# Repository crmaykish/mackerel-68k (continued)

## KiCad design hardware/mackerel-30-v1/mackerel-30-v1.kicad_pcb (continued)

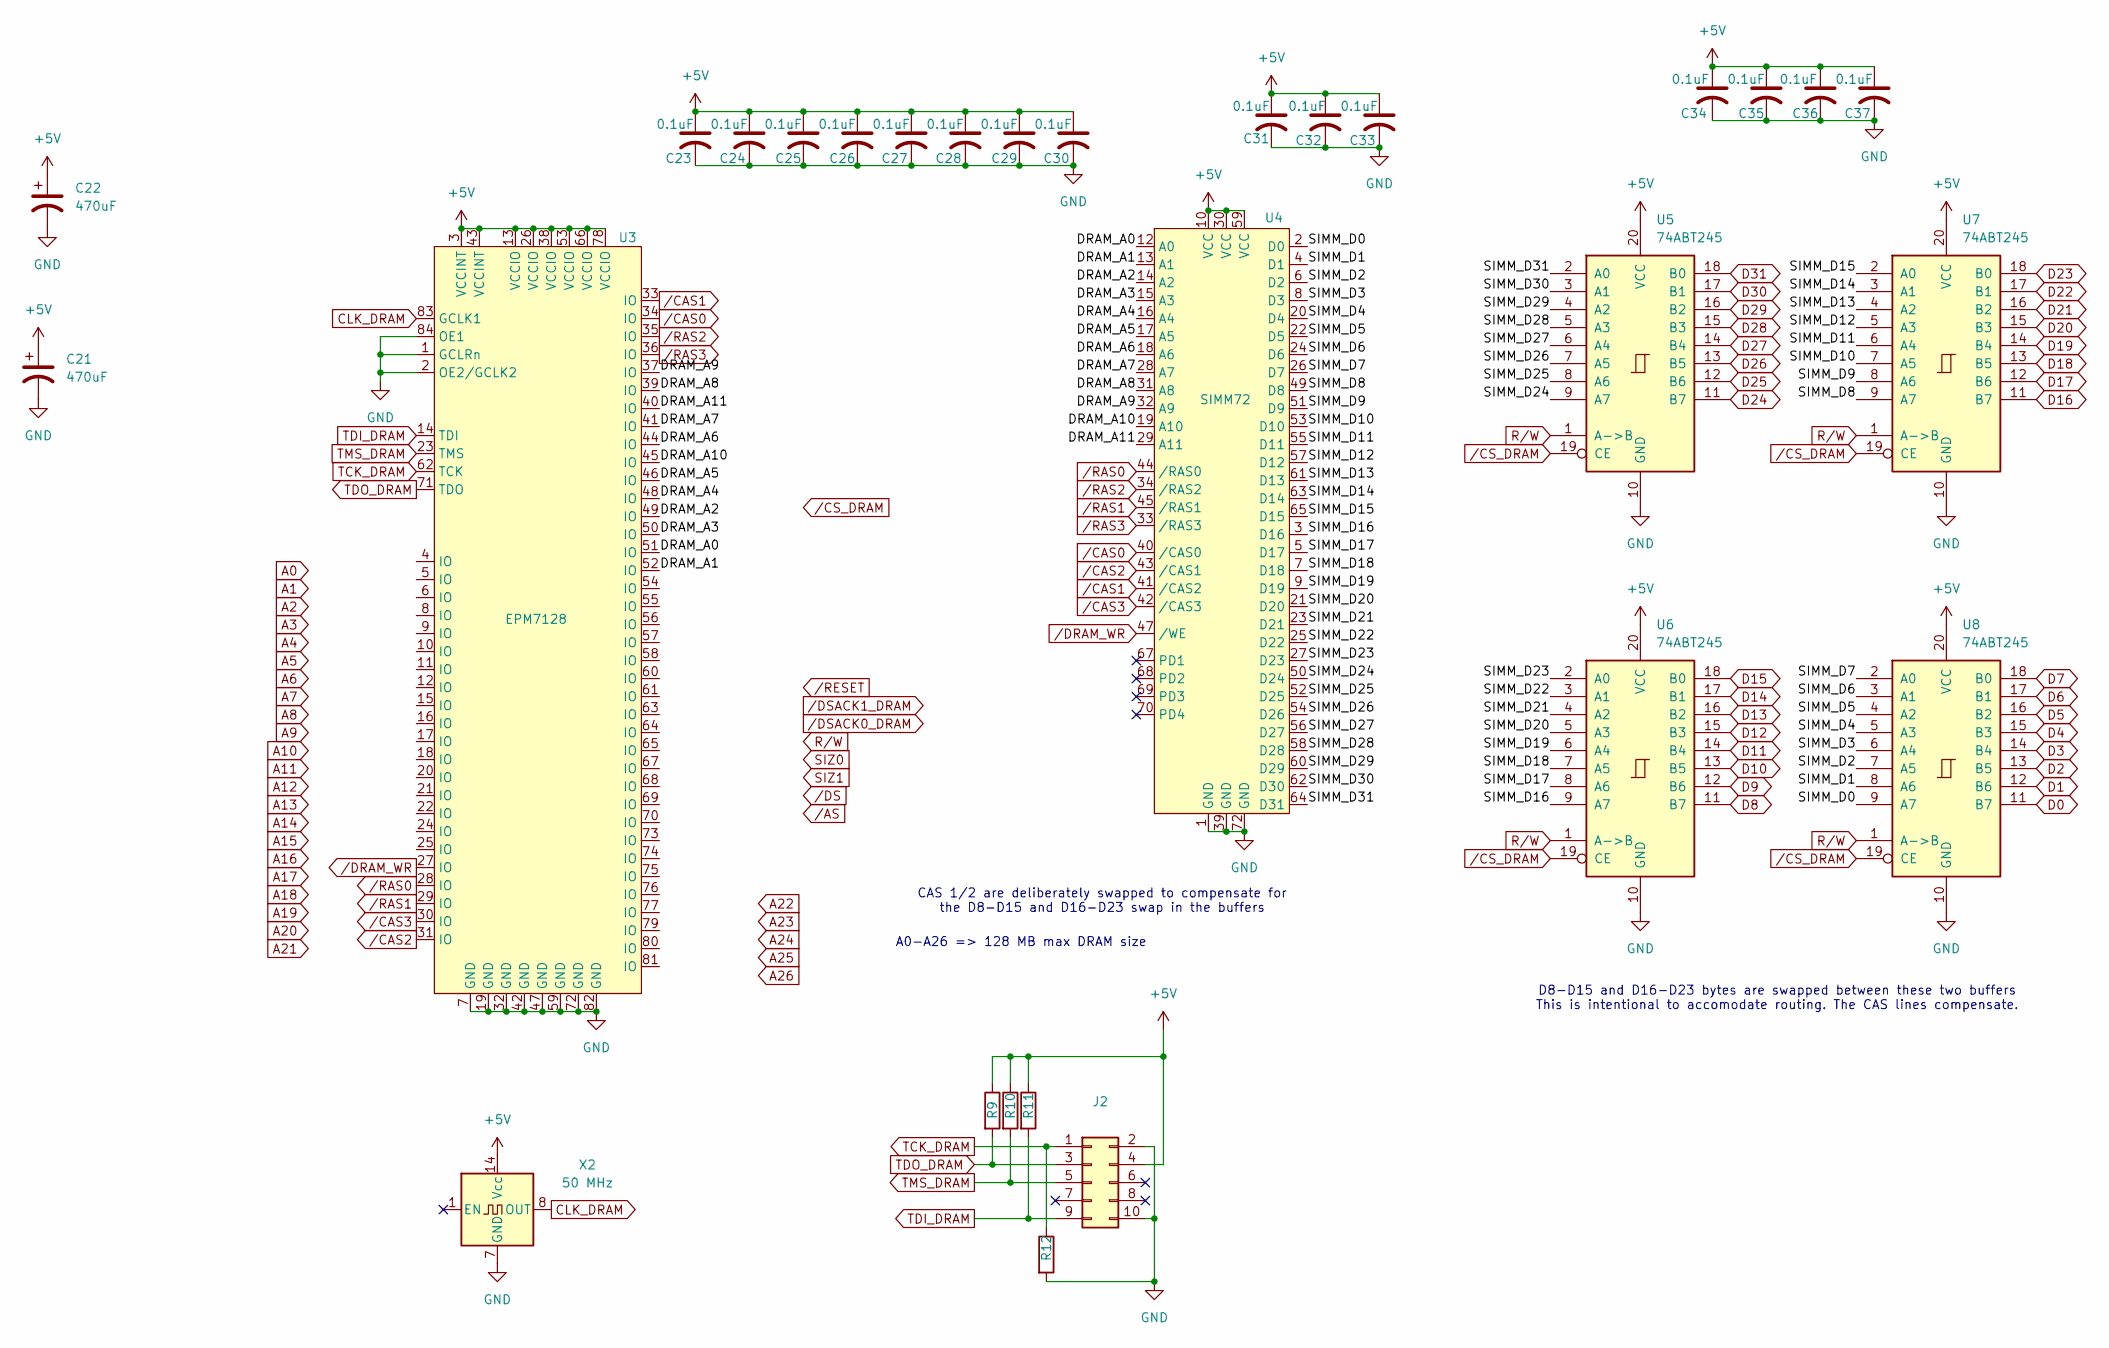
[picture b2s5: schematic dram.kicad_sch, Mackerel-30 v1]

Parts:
C21, C22: 470uF; CP_Radial_D8.0mm_P3.50mm
C23, C24, C25, C26, C27, C28, C29, C30, C31, C32, C33, C34, C35, C36, C37: 0.1uF; C_1206_3216Metric_Pad1.33x1.80mm_HandSolder
J2: Conn_02x05_Odd_Even; IDC-Header_2x05_P2.54mm_Vertical
R9, R10, R11, R12: 4k7; R_1206_3216Metric_Pad1.30x1.75mm_HandSolder
U3: EPM7128; PLCC-84_THT-Socket
U4: SIMM72; SIMM-72
U5, U6, U7, U8: 74ABT245; DIP-20_W7.62mm_Socket_LongPads
X2: 50 MHz; Oscillator_DIP-14

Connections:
+5V: C21.1, C22.1, C23.1, C24.1, C25.1, C26.1, C27.1, C28.1, C29.1, C30.1, C31.1, C32.1, C33.1, C34.1, C35.1, C36.1, C37.1, J2.4, R9.1, R10.1, R11.1, U3.3 (VCCINT), U3.13 (VCCIO), U3.26 (VCCIO), U3.38 (VCCIO), U3.43 (VCCINT), U3.53 (VCCIO), U3.66 (VCCIO), U3.78 (VCCIO), U4.10 (VCC), U4.30 (VCC), U4.59 (VCC), U5.20 (VCC), U6.20 (VCC), U7.20 (VCC), U8.20 (VCC), X2.14 (Vcc); also elsewhere on the board
/DRAM/DRAM_A0: U3.51 (IO), U4.12 (A0)
/DRAM/DRAM_A1: U3.52 (IO), U4.13 (A1)
/DRAM/DRAM_A2: U3.49 (IO), U4.14 (A2)
/DRAM/DRAM_A3: U3.50 (IO), U4.15 (A3)
/DRAM/DRAM_A4: U3.48 (IO), U4.16 (A4)
/DRAM/DRAM_A5: U3.46 (IO), U4.17 (A5)
/DRAM/DRAM_A6: U3.44 (IO), U4.18 (A6)
/DRAM/DRAM_A7: U3.41 (IO), U4.28 (A7)
/DRAM/DRAM_A8: U3.39 (IO), U4.31 (A8)
/DRAM/DRAM_A9: U3.37 (IO), U4.32 (A9)
/DRAM/DRAM_A10: U3.45 (IO), U4.19 (A10)
/DRAM/DRAM_A11: U3.40 (IO), U4.29 (A11)
/DRAM/SIMM_D0: U4.2 (D0), U8.9 (A7)
/DRAM/SIMM_D1: U4.4 (D1), U8.8 (A6)
/DRAM/SIMM_D2: U4.6 (D2), U8.7 (A5)
/DRAM/SIMM_D3: U4.8 (D3), U8.6 (A4)
/DRAM/SIMM_D4: U4.20 (D4), U8.5 (A3)
/DRAM/SIMM_D5: U4.22 (D5), U8.4 (A2)
/DRAM/SIMM_D6: U4.24 (D6), U8.3 (A1)
/DRAM/SIMM_D7: U4.26 (D7), U8.2 (A0)
/DRAM/SIMM_D8: U4.49 (D8), U7.9 (A7)
/DRAM/SIMM_D9: U4.51 (D9), U7.8 (A6)
/DRAM/SIMM_D10: U4.53 (D10), U7.7 (A5)
/DRAM/SIMM_D11: U4.55 (D11), U7.6 (A4)
/DRAM/SIMM_D12: U4.57 (D12), U7.5 (A3)
/DRAM/SIMM_D13: U4.61 (D13), U7.4 (A2)
/DRAM/SIMM_D14: U4.63 (D14), U7.3 (A1)
/DRAM/SIMM_D15: U4.65 (D15), U7.2 (A0)
/DRAM/SIMM_D16: U4.3 (D16), U6.9 (A7)
/DRAM/SIMM_D17: U4.5 (D17), U6.8 (A6)
/DRAM/SIMM_D18: U4.7 (D18), U6.7 (A5)
/DRAM/SIMM_D19: U4.9 (D19), U6.6 (A4)
/DRAM/SIMM_D20: U4.21 (D20), U6.5 (A3)
/DRAM/SIMM_D21: U4.23 (D21), U6.4 (A2)
/DRAM/SIMM_D22: U4.25 (D22), U6.3 (A1)
/DRAM/SIMM_D23: U4.27 (D23), U6.2 (A0)
/DRAM/SIMM_D24: U4.50 (D24), U5.9 (A7)
/DRAM/SIMM_D25: U4.52 (D25), U5.8 (A6)
/DRAM/SIMM_D26: U4.54 (D26), U5.7 (A5)
/DRAM/SIMM_D27: U4.56 (D27), U5.6 (A4)
/DRAM/SIMM_D28: U4.58 (D28), U5.5 (A3)
/DRAM/SIMM_D29: U4.60 (D29), U5.4 (A2)
/DRAM/SIMM_D30: U4.62 (D30), U5.3 (A1)
/DRAM/SIMM_D31: U4.64 (D31), U5.2 (A0)
CLK_DRAM: U3.83 (GCLK1), X2.8 (OUT)
D0: U8.11 (B7); also elsewhere on the board
D1: U8.12 (B6); also elsewhere on the board
D2: U8.13 (B5); also elsewhere on the board
D3: U8.14 (B4); also elsewhere on the board
D4: U8.15 (B3); also elsewhere on the board
D5: U8.16 (B2); also elsewhere on the board
D6: U8.17 (B1); also elsewhere on the board
D7: U8.18 (B0); also elsewhere on the board
D8: U6.11 (B7); also elsewhere on the board
D9: U6.12 (B6); also elsewhere on the board
D10: U6.13 (B5); also elsewhere on the board
D11: U6.14 (B4); also elsewhere on the board
D12: U6.15 (B3); also elsewhere on the board
D13: U6.16 (B2); also elsewhere on the board
D14: U6.17 (B1); also elsewhere on the board
D15: U6.18 (B0); also elsewhere on the board
D16: U7.11 (B7); also elsewhere on the board
D17: U7.12 (B6); also elsewhere on the board
D18: U7.13 (B5); also elsewhere on the board
D19: U7.14 (B4); also elsewhere on the board
D20: U7.15 (B3); also elsewhere on the board
D21: U7.16 (B2); also elsewhere on the board
D22: U7.17 (B1); also elsewhere on the board
D23: U7.18 (B0); also elsewhere on the board
D24: U5.11 (B7); also elsewhere on the board
D25: U5.12 (B6); also elsewhere on the board
D26: U5.13 (B5); also elsewhere on the board
D27: U5.14 (B4); also elsewhere on the board
D28: U5.15 (B3); also elsewhere on the board
D29: U5.16 (B2); also elsewhere on the board
D30: U5.17 (B1); also elsewhere on the board
D31: U5.18 (B0); also elsewhere on the board
GND: C21.2, C22.2, C23.2, C24.2, C25.2, C26.2, C27.2, C28.2, C29.2, C30.2, C31.2, C32.2, C33.2, C34.2, C35.2, C36.2, C37.2, J2.2, J2.10, R12.2, U3.1 (GCLRn), U3.2 (OE2/GCLK2), U3.7 (GND), U3.19 (GND), U3.32 (GND), U3.42 (GND), U3.47 (GND), U3.59 (GND), U3.72 (GND), U3.82 (GND), U3.84 (OE1), U4.1 (GND), U4.39 (GND), U4.72 (GND), U5.10 (GND), U6.10 (GND), U7.10 (GND), U8.10 (GND), X2.7 (GND); also elsewhere on the board
R/W: U5.1 (A->B), U6.1 (A->B), U7.1 (A->B), U8.1 (A->B); also elsewhere on the board
TCK_DRAM: J2.1, R12.1, U3.62 (TCK)
TDI_DRAM: J2.9, R11.2, U3.14 (TDI)
TDO_DRAM: J2.3, R9.2, U3.71 (TDO)
TMS_DRAM: J2.5, R10.2, U3.23 (TMS)
/CAS0: U3.34 (IO), U4.40 (/CAS0)
/CAS1: U3.33 (IO), U4.41 (/CAS2)
/CAS2: U3.31 (IO), U4.43 (/CAS1)
/CAS3: U3.30 (IO), U4.42 (/CAS3)
/CS_DRAM: U5.19 (CE), U6.19 (CE), U7.19 (CE), U8.19 (CE)
/DRAM_WR: U3.27 (IO), U4.47 (/WE)
/RAS0: U3.28 (IO), U4.44 (/RAS0)
/RAS1: U3.29 (IO), U4.45 (/RAS1)
/RAS2: U3.35 (IO), U4.34 (/RAS2)
/RAS3: U3.36 (IO), U4.33 (/RAS3)

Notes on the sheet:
A0-A26 => 128 MB max DRAM size
CAS 1/2 are deliberately swapped to compensate for the D8-D15 and D16-D23 swap in the buffers
D8-D15 and D16-D23 bytes are swapped between these two buffers This is intentional to accomodate routing. The CAS lines compensate.

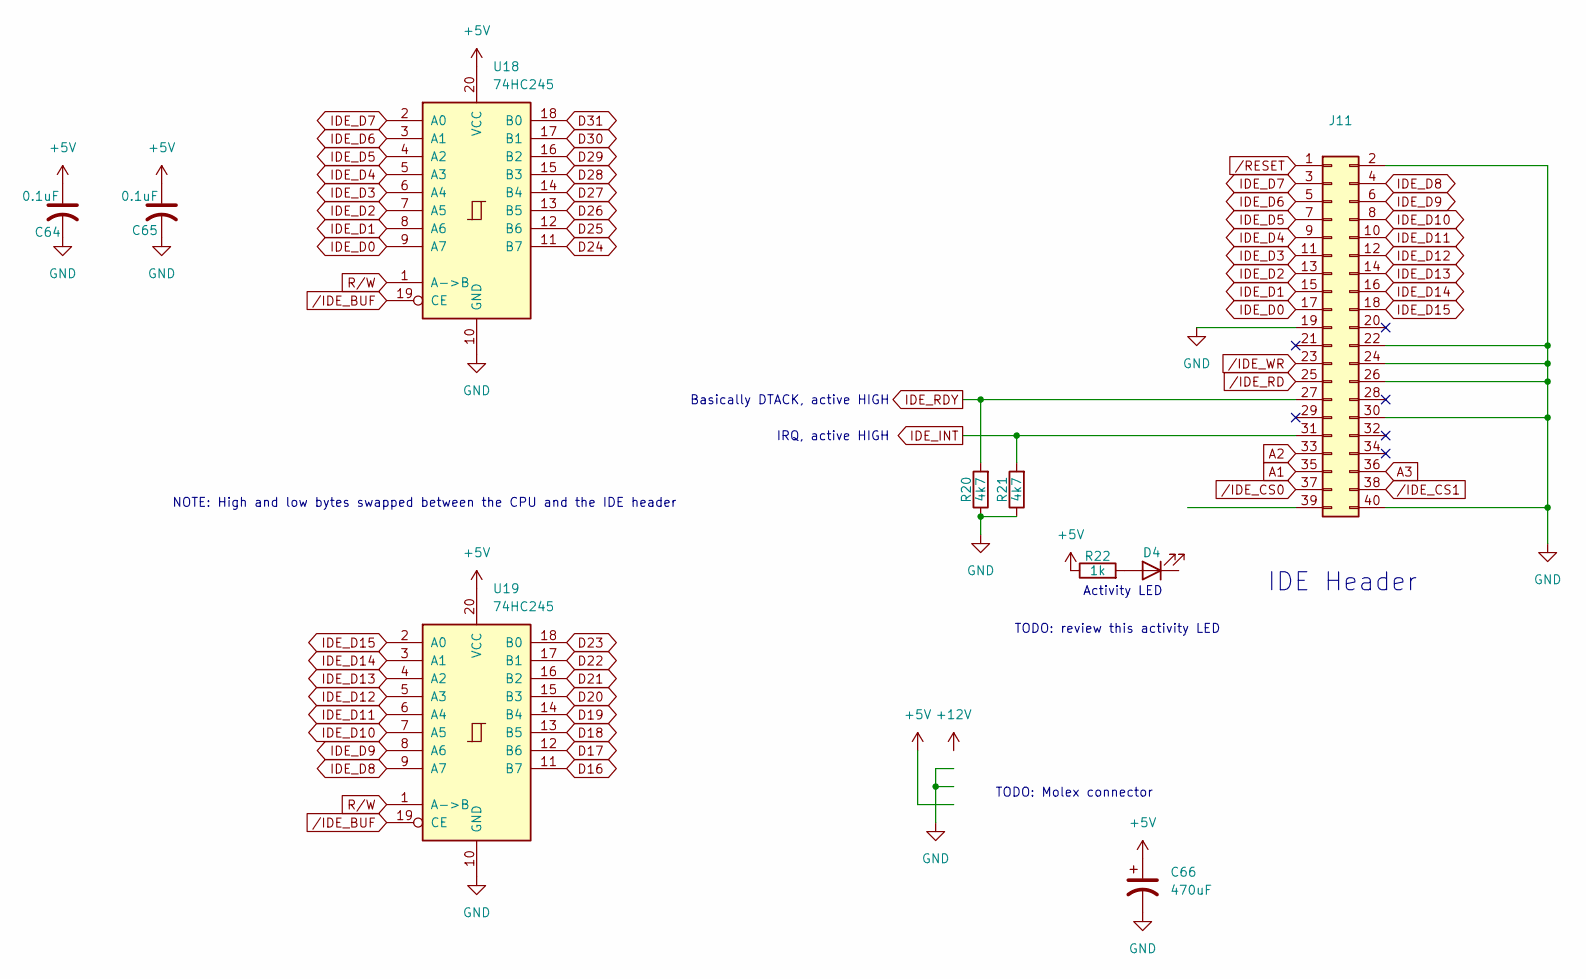
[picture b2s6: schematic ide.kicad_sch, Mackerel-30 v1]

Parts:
C64, C65: 0.1uF; C_1206_3216Metric_Pad1.33x1.80mm_HandSolder
C66: 470uF; CP_Radial_D8.0mm_P3.50mm
D4: LED; LED_D5.0mm
J11: Conn_02x20_Odd_Even; IDC-Header_2x20_P2.54mm_Vertical
R20, R21: 4k7; R_1206_3216Metric_Pad1.30x1.75mm_HandSolder
R22: 1k; R_1206_3216Metric_Pad1.30x1.75mm_HandSolder
U18, U19: 74HC245; DIP-20_W7.62mm_Socket

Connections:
+5V: C64.1, C65.1, C66.1, R22.1, U18.20 (VCC), U19.20 (VCC); also elsewhere on the board
A1: J11.35; also elsewhere on the board
A2: J11.33; also elsewhere on the board
A3: J11.36; also elsewhere on the board
D16: U19.11 (B7); also elsewhere on the board
D17: U19.12 (B6); also elsewhere on the board
D18: U19.13 (B5); also elsewhere on the board
D19: U19.14 (B4); also elsewhere on the board
D20: U19.15 (B3); also elsewhere on the board
D21: U19.16 (B2); also elsewhere on the board
D22: U19.17 (B1); also elsewhere on the board
D23: U19.18 (B0); also elsewhere on the board
D24: U18.11 (B7); also elsewhere on the board
D25: U18.12 (B6); also elsewhere on the board
D26: U18.13 (B5); also elsewhere on the board
D27: U18.14 (B4); also elsewhere on the board
D28: U18.15 (B3); also elsewhere on the board
D29: U18.16 (B2); also elsewhere on the board
D30: U18.17 (B1); also elsewhere on the board
D31: U18.18 (B0); also elsewhere on the board
GND: C64.2, C65.2, C66.2, J11.2, J11.19, J11.22, J11.24, J11.26, J11.30, J11.40, R20.1, R21.1, U18.10 (GND), U19.10 (GND); also elsewhere on the board
IDE_D0: J11.17, U18.9 (A7)
IDE_D1: J11.15, U18.8 (A6)
IDE_D2: J11.13, U18.7 (A5)
IDE_D3: J11.11, U18.6 (A4)
IDE_D4: J11.9, U18.5 (A3)
IDE_D5: J11.7, U18.4 (A2)
IDE_D6: J11.5, U18.3 (A1)
IDE_D7: J11.3, U18.2 (A0)
IDE_D8: J11.4, U19.9 (A7)
IDE_D9: J11.6, U19.8 (A6)
IDE_D10: J11.8, U19.7 (A5)
IDE_D11: J11.10, U19.6 (A4)
IDE_D12: J11.12, U19.5 (A3)
IDE_D13: J11.14, U19.4 (A2)
IDE_D14: J11.16, U19.3 (A1)
IDE_D15: J11.18, U19.2 (A0)
IDE_INT: J11.31, R21.2
IDE_RDY: J11.27, R20.2
unnamed: D4.2 (A_2), R22.2
R/W: U18.1 (A->B), U19.1 (A->B); also elsewhere on the board
/IDE_BUF: U18.19 (CE), U19.19 (CE)
/IDE_CS0: J11.37
/IDE_CS1: J11.38
/IDE_RD: J11.25
/IDE_WR: J11.23
/RESET: J11.1; also elsewhere on the board

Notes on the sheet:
IDE Header
TODO: Molex connector
IRQ, active HIGH
NOTE: High and low bytes swapped between the CPU and the IDE header
TODO: review this activity LED
Basically DTACK, active HIGH
Activity LED

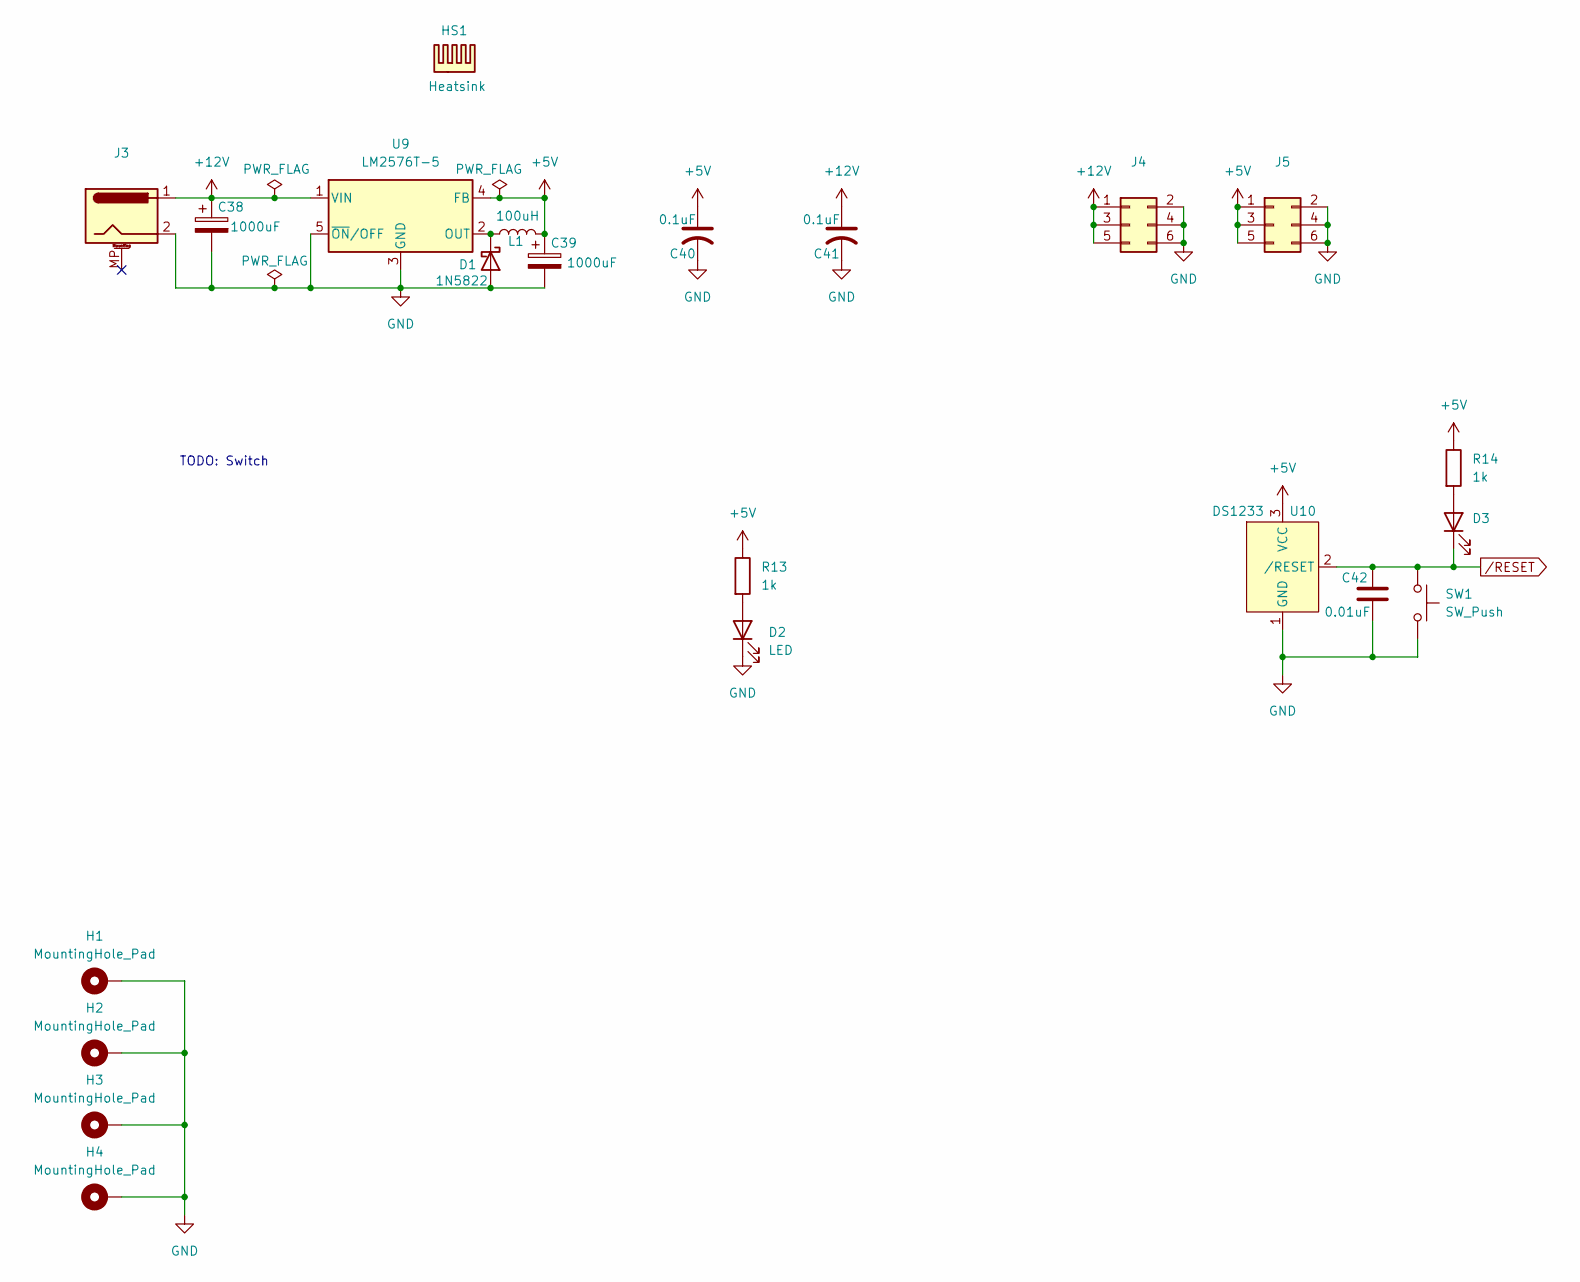
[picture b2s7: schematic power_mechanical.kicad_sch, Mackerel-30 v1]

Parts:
C38, C39: 1000uF; CP_Radial_D10.0mm_P5.00mm
C40, C41: 0.1uF; C_1206_3216Metric_Pad1.33x1.80mm_HandSolder
C42: 0.01uF; C_1206_3216Metric_Pad1.33x1.80mm_HandSolder
D1: 1N5822; D_DO-27_P15.24mm_Horizontal
D2, D3: LED; LED_D5.0mm
H1, H2, H3, H4: MountingHole_Pad; MountingHole_3.2mm_M3_Pad_Via
HS1: Heatsink; Heatsink_Stonecold_HS-S02_13.21x9.53mm
J3: Barrel_Jack_MountingPin; BarrelJack_Horizontal
J4, J5: Conn_02x03_Odd_Even; PinHeader_2x03_P2.54mm_Vertical
L1: 100uH; L_Radial_D10.0mm_P5.00mm_Fastron_07M
R13, R14: 1k; R_1206_3216Metric_Pad1.30x1.75mm_HandSolder
SW1: SW_Push; SW_PUSH_6mm_H5mm
U9: LM2576T-5; TO-220-5_Vertical
U10: DS1233; TO-92L_Wide

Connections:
+5V: C39.1, C40.1, J5.1, J5.3, J5.5, L1.2, R13.1, R14.1, U9.4 (FB), U10.3 (VCC); also elsewhere on the board
+12V: C38.1, C41.1, J3.1, J4.1, J4.3, J4.5, U9.1 (VIN)
GND: C38.2, C39.2, C40.2, C41.2, C42.2, D1.2 (A), D2.1 (K), H1.1 (1_1), H2.1 (1_1), H3.1 (1_1), H4.1 (1_1), J3.2, J4.2, J4.4, J4.6, J5.2, J5.4, J5.6, SW1.2, U9.3 (GND), U9.5 (~ON/OFF), U10.1 (GND); also elsewhere on the board
unnamed: D1.1 (K), L1.1, U9.2 (OUT)
unnamed: D2.2 (A), R13.2
unnamed: D3.2 (A), R14.2
/RESET: C42.1, D3.1 (K), SW1.1, U10.2 (/RESET); also elsewhere on the board

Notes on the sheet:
TODO: Switch

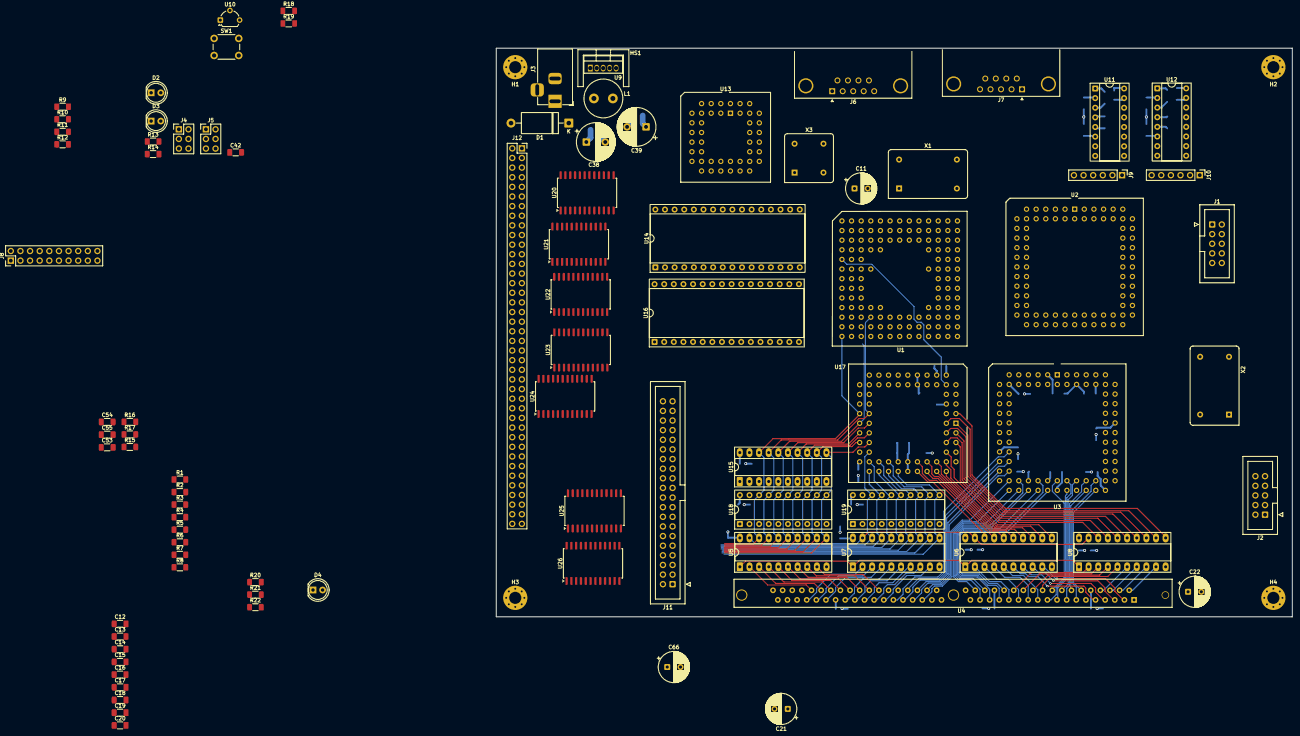
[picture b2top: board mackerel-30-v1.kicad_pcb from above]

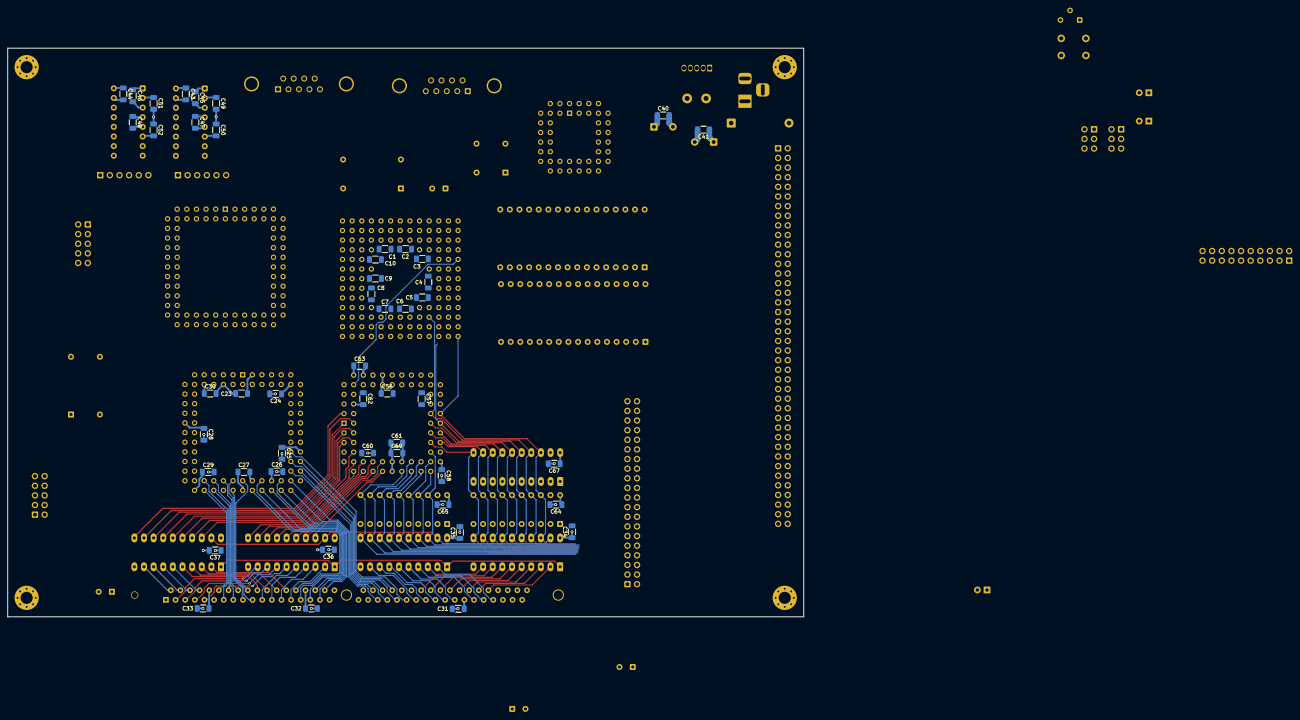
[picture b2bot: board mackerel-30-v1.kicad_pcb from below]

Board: 4 copper layers, 210.0 x 150.0 mm, 141 parts (48 on the bottom side), 215 nets.

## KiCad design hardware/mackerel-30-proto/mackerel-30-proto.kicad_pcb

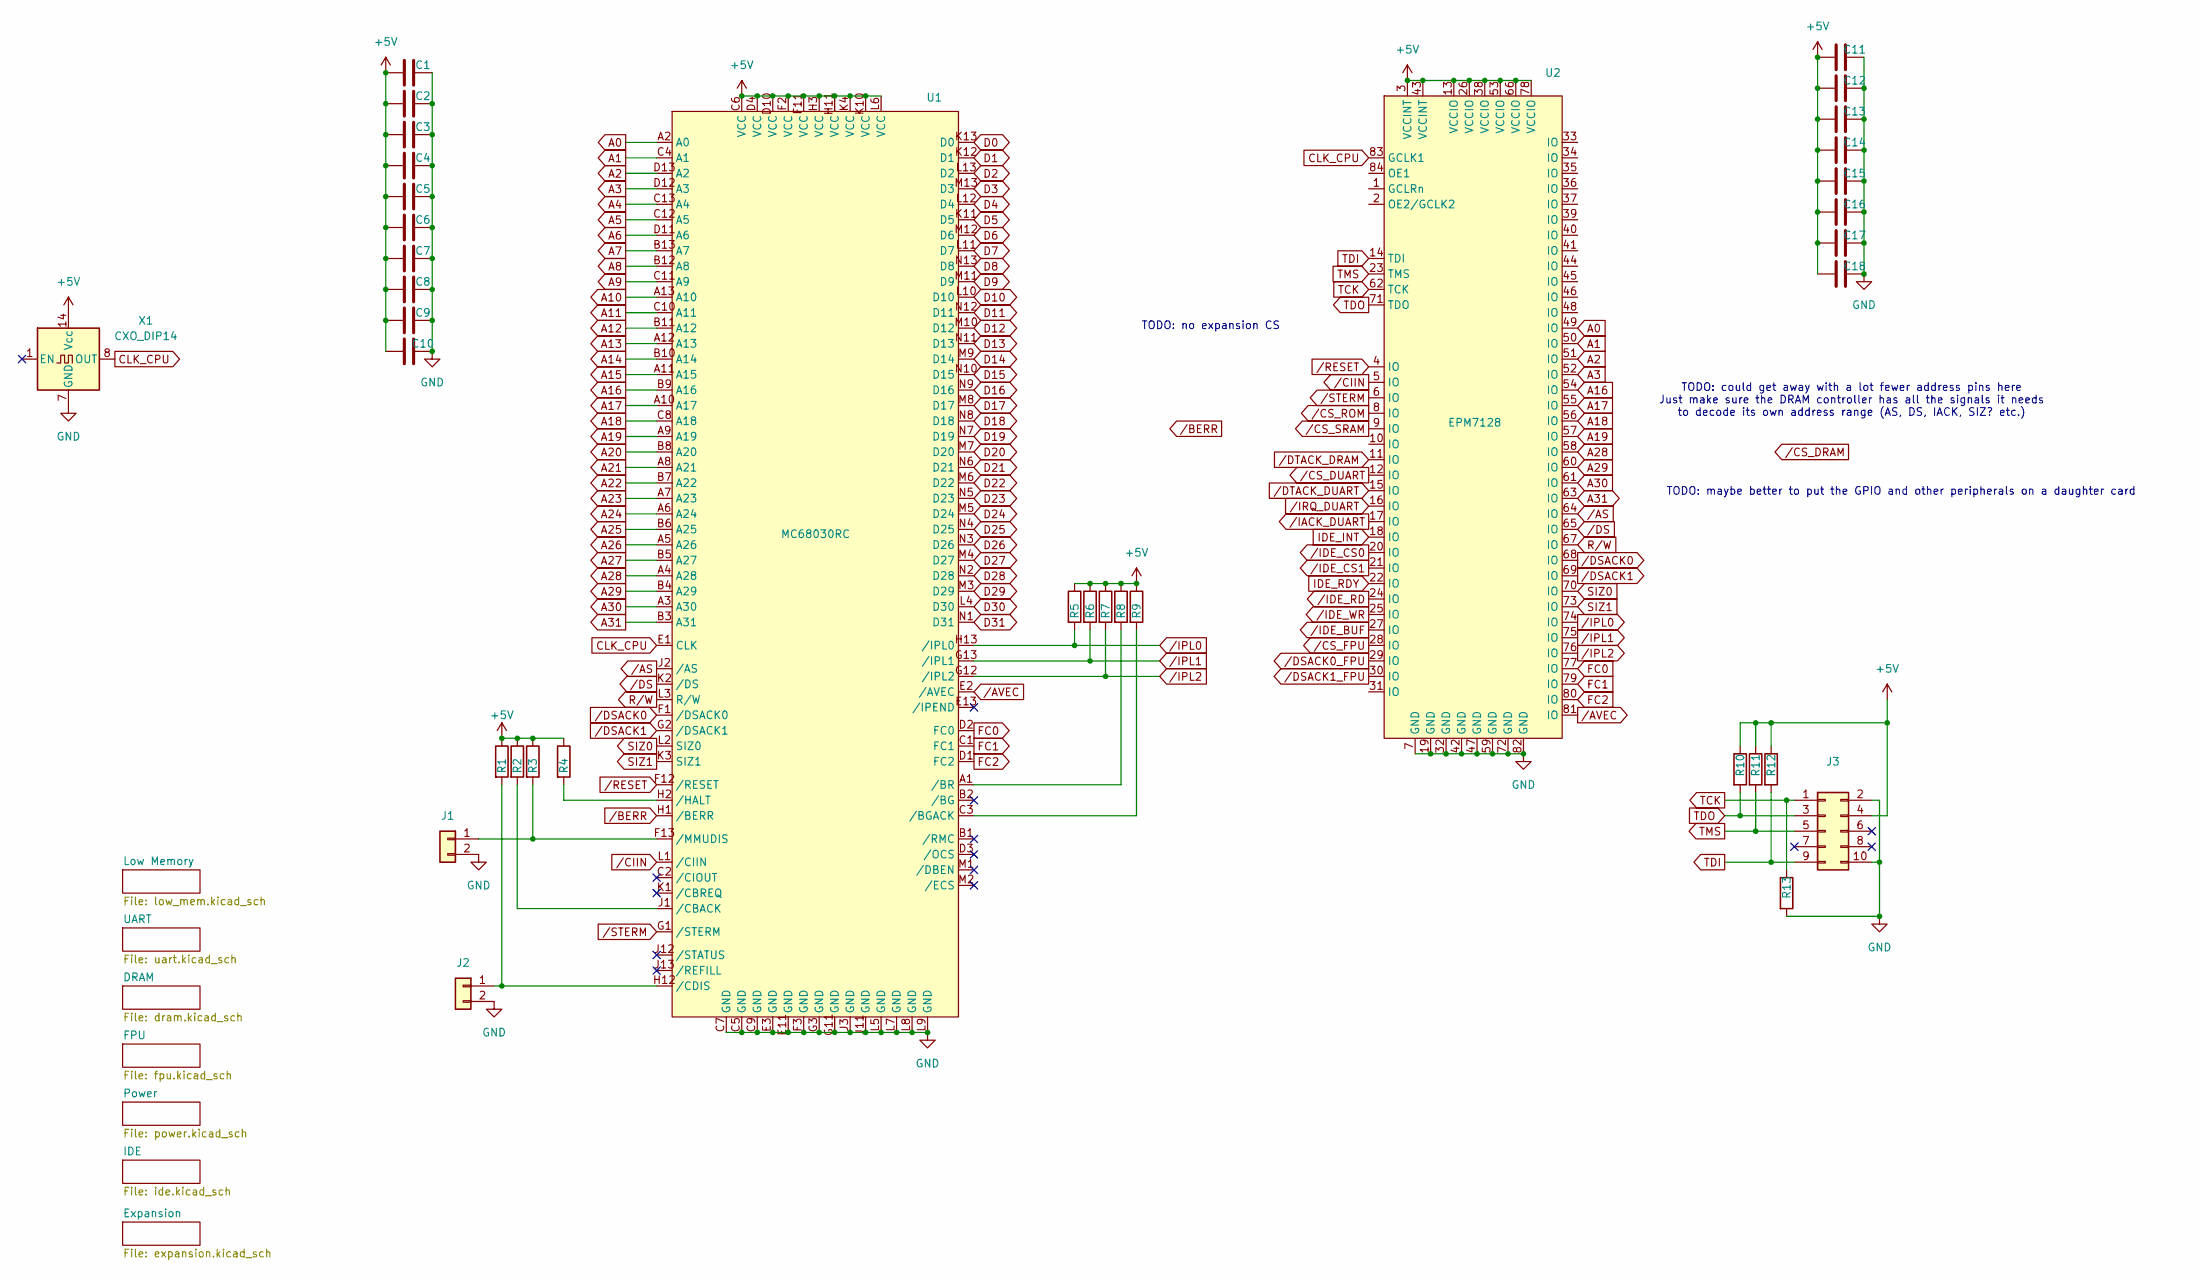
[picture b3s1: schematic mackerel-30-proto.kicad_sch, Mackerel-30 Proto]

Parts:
C1, C2, C3, C4, C5, C6, C7, C8, C9, C10: 0.1uF; C_1206_3216Metric_Pad1.33x1.80mm_HandSolder
C11, C12, C13, C14, C15, C16, C17, C18: 0.1uF; C_Disc_D4.3mm_W1.9mm_P5.00mm
J1, J2: Conn_01x02; PinHeader_1x02_P2.54mm_Vertical
J3: Conn_02x05_Odd_Even; IDC-Header_2x05_P2.54mm_Vertical
R1, R2, R3, R4, R5, R6, R7, R8, R9: 4k7; R_Axial_DIN0207_L6.3mm_D2.5mm_P7.62mm_Horizontal
R10, R11, R12, R13: R; R_Axial_DIN0207_L6.3mm_D2.5mm_P7.62mm_Horizontal
U1: MC68030RC; PGA169
U2: EPM7128; PLCC-84_THT-Socket
X1: CXO_DIP14; Oscillator_DIP-14

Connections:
+5V: C1.1, C2.1, C3.1, C4.1, C5.1, C6.1, C7.1, C8.1, C9.1, C10.1, C11.1, C12.1, C13.1, C14.1, C15.1, C16.1, C17.1, C18.1, J3.4, R1.1, R2.1, R3.1, R4.1, R5.1, R6.1, R7.1, R8.1, R9.1, R10.1, R11.1, R12.1, U1.C6 (VCC), U1.D4 (VCC), U1.D10 (VCC), U1.F2 (VCC), U1.F11 (VCC), U1.H3 (VCC), U1.H11 (VCC), U1.K4 (VCC), U1.K10 (VCC), U1.L6 (VCC), U2.3 (VCCINT), U2.13 (VCCIO), U2.26 (VCCIO), U2.38 (VCCIO), U2.43 (VCCINT), U2.53 (VCCIO), U2.66 (VCCIO), U2.78 (VCCIO), X1.14 (Vcc); also elsewhere on the board
A0: U1.A2 (A0), U2.49 (IO); also elsewhere on the board
A1: U1.C4 (A1), U2.50 (IO); also elsewhere on the board
A2: U1.D13 (A2), U2.51 (IO); also elsewhere on the board
A3: U1.D12 (A3), U2.52 (IO); also elsewhere on the board
A4: U1.C13 (A4); also elsewhere on the board
A5: U1.C12 (A5); also elsewhere on the board
A6: U1.D11 (A6); also elsewhere on the board
A7: U1.B13 (A7); also elsewhere on the board
A8: U1.B12 (A8); also elsewhere on the board
A9: U1.C11 (A9); also elsewhere on the board
A10: U1.A13 (A10); also elsewhere on the board
A11: U1.C10 (A11); also elsewhere on the board
A12: U1.B11 (A12); also elsewhere on the board
A13: U1.A12 (A13); also elsewhere on the board
A14: U1.B10 (A14); also elsewhere on the board
A15: U1.A11 (A15); also elsewhere on the board
A16: U1.B9 (A16), U2.54 (IO); also elsewhere on the board
A17: U1.A10 (A17), U2.55 (IO); also elsewhere on the board
A18: U1.C8 (A18), U2.56 (IO); also elsewhere on the board
A19: U1.A9 (A19), U2.57 (IO); also elsewhere on the board
A20: U1.B8 (A20); also elsewhere on the board
A21: U1.A8 (A21); also elsewhere on the board
A22: U1.B7 (A22); also elsewhere on the board
A23: U1.A7 (A23); also elsewhere on the board
A24: U1.A6 (A24); also elsewhere on the board
A25: U1.B6 (A25); also elsewhere on the board
A26: U1.A5 (A26); also elsewhere on the board
A27: U1.B5 (A27); also elsewhere on the board
A28: U1.A4 (A28), U2.58 (IO)
A29: U1.B4 (A29), U2.60 (IO)
A30: U1.A3 (A30), U2.61 (IO)
A31: U1.B3 (A31), U2.63 (IO)
CLK_CPU: U1.E1 (CLK), U2.83 (GCLK1), X1.8 (OUT); also elsewhere on the board
D0: U1.K13 (D0); also elsewhere on the board
D1: U1.K12 (D1); also elsewhere on the board
D2: U1.L13 (D2); also elsewhere on the board
D3: U1.M13 (D3); also elsewhere on the board
D4: U1.L12 (D4); also elsewhere on the board
D5: U1.K11 (D5); also elsewhere on the board
D6: U1.M12 (D6); also elsewhere on the board
D7: U1.L11 (D7); also elsewhere on the board
D8: U1.N13 (D8); also elsewhere on the board
D9: U1.M11 (D9); also elsewhere on the board
D10: U1.L10 (D10); also elsewhere on the board
D11: U1.N12 (D11); also elsewhere on the board
D12: U1.M10 (D12); also elsewhere on the board
D13: U1.N11 (D13); also elsewhere on the board
D14: U1.M9 (D14); also elsewhere on the board
D15: U1.N10 (D15); also elsewhere on the board
D16: U1.N9 (D16); also elsewhere on the board
D17: U1.M8 (D17); also elsewhere on the board
D18: U1.N8 (D18); also elsewhere on the board
D19: U1.N7 (D19); also elsewhere on the board
D20: U1.M7 (D20); also elsewhere on the board
D21: U1.N6 (D21); also elsewhere on the board
D22: U1.M6 (D22); also elsewhere on the board
D23: U1.N5 (D23); also elsewhere on the board
D24: U1.M5 (D24); also elsewhere on the board
D25: U1.N4 (D25); also elsewhere on the board
D26: U1.N3 (D26); also elsewhere on the board
D27: U1.M4 (D27); also elsewhere on the board
D28: U1.N2 (D28); also elsewhere on the board
D29: U1.M3 (D29); also elsewhere on the board
D30: U1.L4 (D30); also elsewhere on the board
D31: U1.N1 (D31); also elsewhere on the board
FC0: U1.D2 (FC0), U2.77 (IO)
FC1: U1.C1 (FC1), U2.79 (IO)
FC2: U1.D1 (FC2), U2.80 (IO)
GND: C1.2, C2.2, C3.2, C4.2, C5.2, C6.2, C7.2, C8.2, C9.2, C10.2, C11.2, C12.2, C13.2, C14.2, C15.2, C16.2, C17.2, C18.2, J1.2, J2.2, J3.2, J3.10, R13.2, U1.C5 (GND), U1.C7 (GND), U1.C9 (GND), U1.E3 (GND), U1.E11 (GND), U1.F3 (GND), U1.G3 (GND), U1.G11 (GND), U1.J3 (GND), U1.J11 (GND), U1.L5 (GND), U1.L7 (GND), U1.L8 (GND), U1.L9 (GND), U2.7 (GND), U2.19 (GND), U2.32 (GND), U2.42 (GND), U2.47 (GND), U2.59 (GND), U2.72 (GND), U2.82 (GND), X1.7 (GND); also elsewhere on the board
IDE_INT: U2.18 (IO); also elsewhere on the board
IDE_RDY: U2.22 (IO); also elsewhere on the board
unnamed: J1.1, R3.2, U1.F13 (/MMUDIS)
unnamed: J2.1, R1.2, U1.H12 (/CDIS)
unnamed: R9.2, U1.C3 (/BGACK)
unnamed: R8.2, U1.A1 (/BR)
unnamed: R2.2, U1.J1 (/CBACK)
unnamed: R4.2, U1.H2 (/HALT)
R/W: U1.L3 (R/W), U2.67 (IO); also elsewhere on the board
SIZ0: U1.L2 (SIZ0), U2.70 (IO)
SIZ1: U1.K3 (SIZ1), U2.73 (IO)
TCK: J3.1, R13.1, U2.62 (TCK)
TDI: J3.9, R12.2, U2.14 (TDI)
TDO: J3.3, R10.2, U2.71 (TDO)
TMS: J3.5, R11.2, U2.23 (TMS)
/AS: U1.J2 (/AS), U2.64 (IO); also elsewhere on the board
/AVEC: U1.E2 (/AVEC), U2.81 (IO)
/BERR: U1.H1 (/BERR)
/CIIN: U1.L1 (/CIIN), U2.5 (IO)
/CS_DUART: U2.12 (IO); also elsewhere on the board
/CS_FPU: U2.28 (IO); also elsewhere on the board
/CS_ROM: U2.8 (IO); also elsewhere on the board
/CS_SRAM: U2.9 (IO); also elsewhere on the board
/DS: U1.K2 (/DS), U2.65 (IO); also elsewhere on the board
/DSACK0: U1.F1 (/DSACK0), U2.68 (IO)
/DSACK0_FPU: U2.29 (IO); also elsewhere on the board
/DSACK1: U1.G2 (/DSACK1), U2.69 (IO)
/DSACK1_FPU: U2.30 (IO); also elsewhere on the board
/DTACK_DRAM: U2.11 (IO)
/DTACK_DUART: U2.15 (IO); also elsewhere on the board
/IACK_DUART: U2.17 (IO); also elsewhere on the board
/IDE_BUF: U2.27 (IO); also elsewhere on the board
/IDE_CS0: U2.20 (IO); also elsewhere on the board
/IDE_CS1: U2.21 (IO); also elsewhere on the board
/IDE_RD: U2.24 (IO); also elsewhere on the board
/IDE_WR: U2.25 (IO); also elsewhere on the board
/IPL0: R5.2, U1.H13 (/IPL0), U2.74 (IO)
/IPL1: R6.2, U1.G13 (/IPL1), U2.75 (IO)
/IPL2: R7.2, U1.G12 (/IPL2), U2.76 (IO)
/IRQ_DUART: U2.16 (IO); also elsewhere on the board
/RESET: U1.F12 (/RESET), U2.4 (IO); also elsewhere on the board
/STERM: U1.G1 (/STERM), U2.6 (IO)

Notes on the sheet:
TODO: maybe better to put the GPIO and other peripherals on a daughter card
TODO: no expansion CS
TODO: could get away with a lot fewer address pins here Just make sure the DRAM controller has all the signals it needs to decode its own address range (AS, DS, IACK, SIZ? etc.)

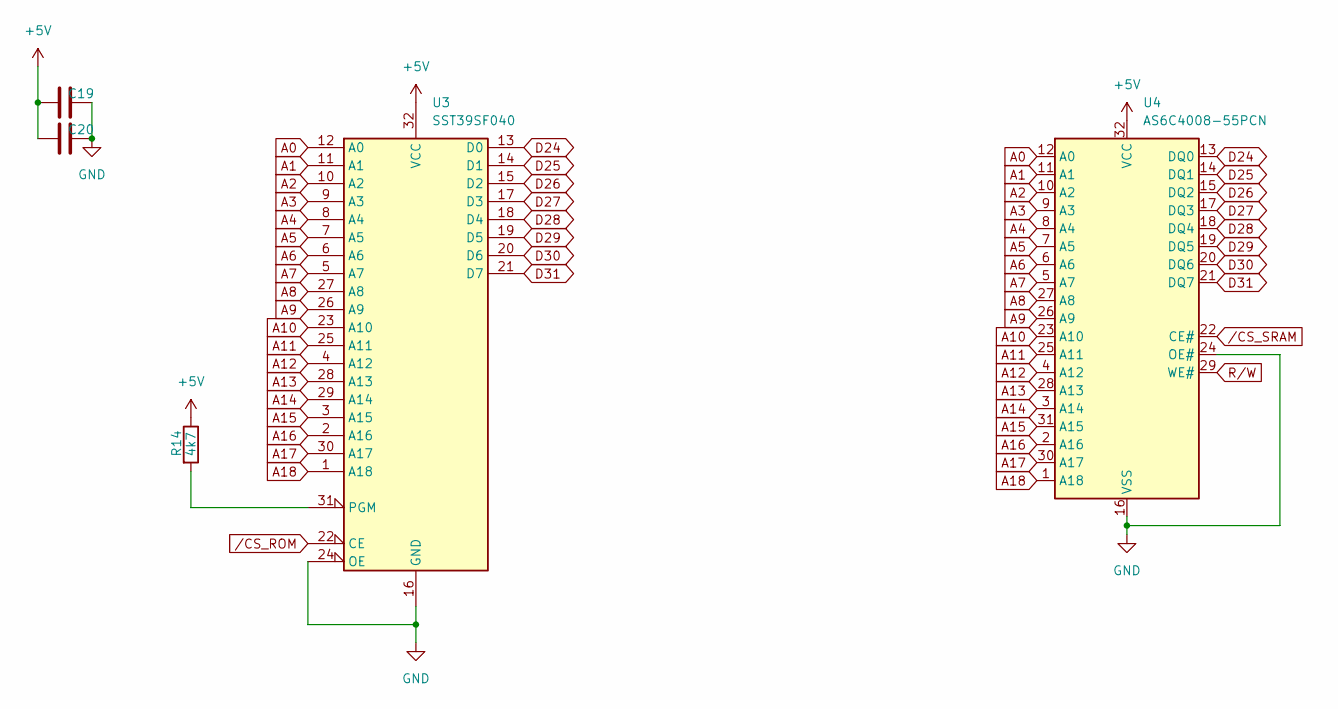
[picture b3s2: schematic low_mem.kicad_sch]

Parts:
C19, C20: 0.1uF; C_Disc_D4.3mm_W1.9mm_P5.00mm
R14: 4k7; R_Axial_DIN0207_L6.3mm_D2.5mm_P7.62mm_Horizontal
U3: SST39SF040; DIP-32_W15.24mm_Socket
U4: AS6C4008-55PCN; DIP-32_W15.24mm_Socket

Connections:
+5V: C19.1, C20.1, R14.1, U3.32 (VCC), U4.32 (VCC); also elsewhere on the board
A0: U3.12 (A0), U4.12 (A0); also elsewhere on the board
A1: U3.11 (A1), U4.11 (A1); also elsewhere on the board
A2: U3.10 (A2), U4.10 (A2); also elsewhere on the board
A3: U3.9 (A3), U4.9 (A3); also elsewhere on the board
A4: U3.8 (A4), U4.8 (A4); also elsewhere on the board
A5: U3.7 (A5), U4.7 (A5); also elsewhere on the board
A6: U3.6 (A6), U4.6 (A6); also elsewhere on the board
A7: U3.5 (A7), U4.5 (A7); also elsewhere on the board
A8: U3.27 (A8), U4.27 (A8); also elsewhere on the board
A9: U3.26 (A9), U4.26 (A9); also elsewhere on the board
A10: U3.23 (A10), U4.23 (A10); also elsewhere on the board
A11: U3.25 (A11), U4.25 (A11); also elsewhere on the board
A12: U3.4 (A12), U4.4 (A12); also elsewhere on the board
A13: U3.28 (A13), U4.28 (A13); also elsewhere on the board
A14: U3.29 (A14), U4.3 (A14); also elsewhere on the board
A15: U3.3 (A15), U4.31 (A15); also elsewhere on the board
A16: U3.2 (A16), U4.2 (A16); also elsewhere on the board
A17: U3.30 (A17), U4.30 (A17); also elsewhere on the board
A18: U3.1 (A18), U4.1 (A18); also elsewhere on the board
D24: U3.13 (D0), U4.13 (DQ0); also elsewhere on the board
D25: U3.14 (D1), U4.14 (DQ1); also elsewhere on the board
D26: U3.15 (D2), U4.15 (DQ2); also elsewhere on the board
D27: U3.17 (D3), U4.17 (DQ3); also elsewhere on the board
D28: U3.18 (D4), U4.18 (DQ4); also elsewhere on the board
D29: U3.19 (D5), U4.19 (DQ5); also elsewhere on the board
D30: U3.20 (D6), U4.20 (DQ6); also elsewhere on the board
D31: U3.21 (D7), U4.21 (DQ7); also elsewhere on the board
GND: C19.2, C20.2, U3.16 (GND), U3.24 (OE), U4.16 (VSS), U4.24 (OE#); also elsewhere on the board
unnamed: R14.2, U3.31 (PGM)
R/W: U4.29 (WE#); also elsewhere on the board
/CS_ROM: U3.22 (CE); also elsewhere on the board
/CS_SRAM: U4.22 (CE#); also elsewhere on the board
